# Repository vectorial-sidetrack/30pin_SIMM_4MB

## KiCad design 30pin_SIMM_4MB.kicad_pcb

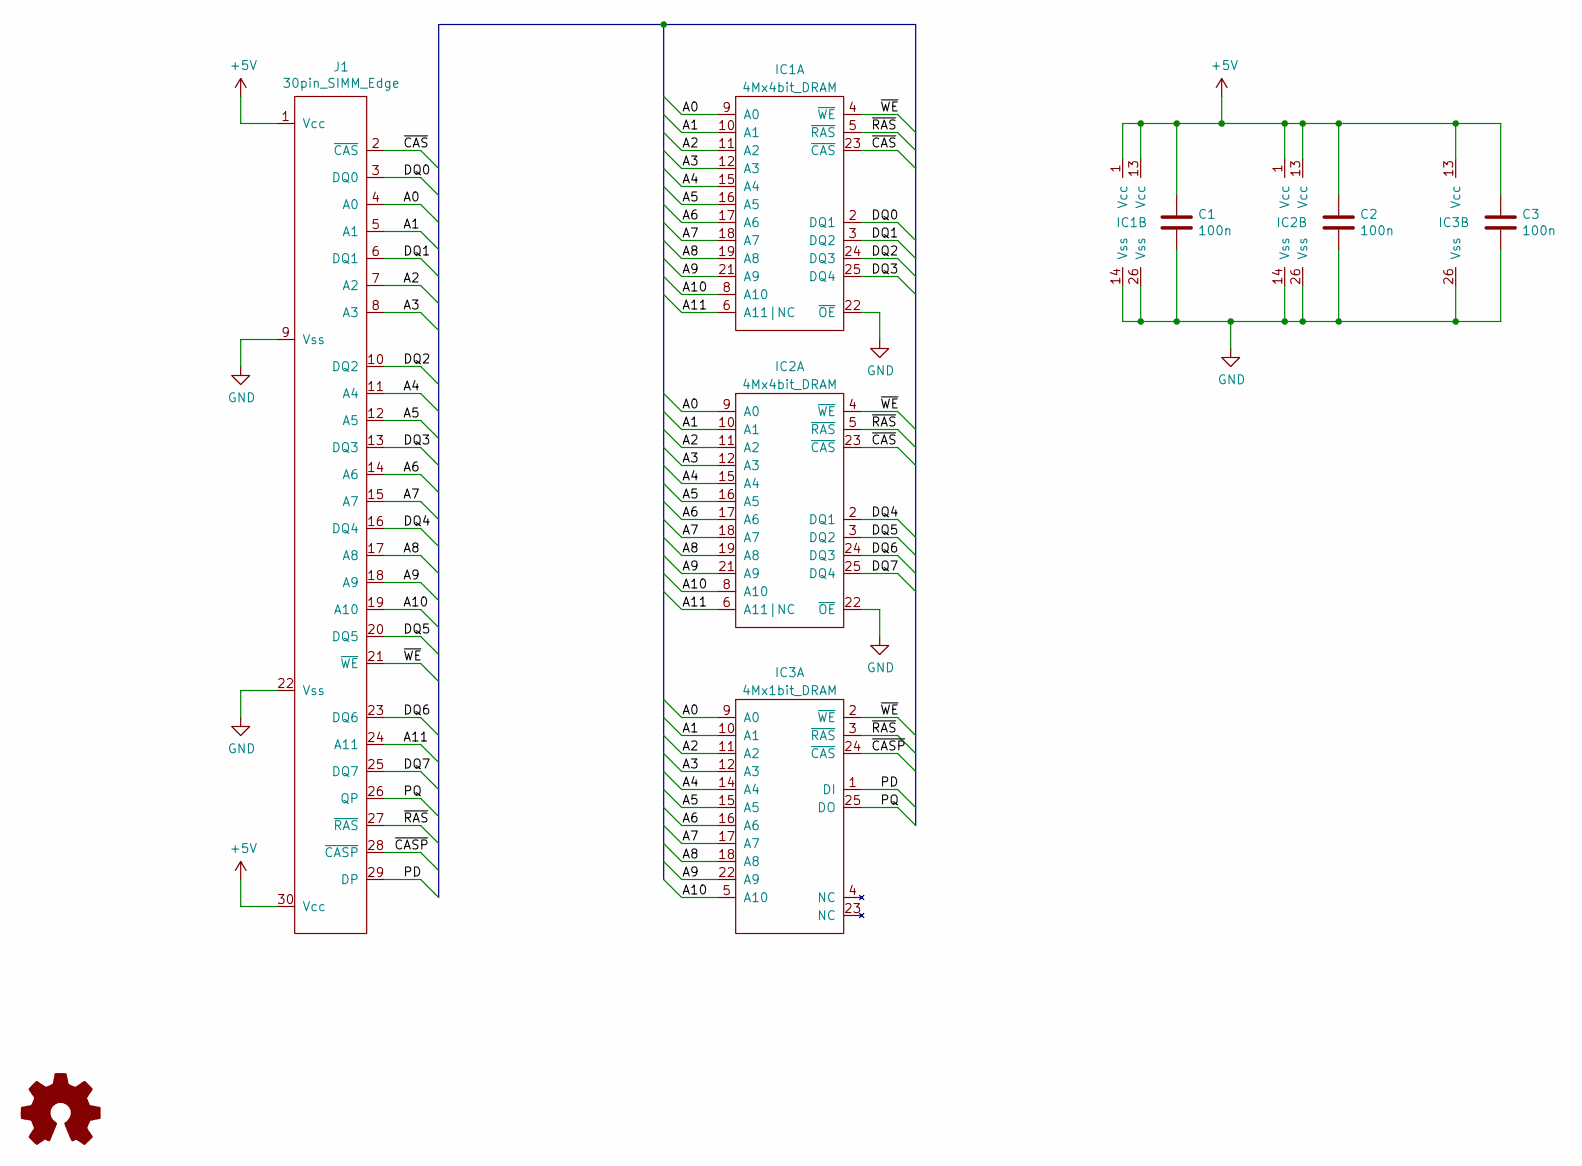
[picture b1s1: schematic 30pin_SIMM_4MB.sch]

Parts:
C1, C2, C3: 100n; C_1206_3216Metric
IC1, IC2: 4Mx4bit_DRAM; 4Mx4bit_DRAM_SOJ-24-26_7.5mm_HandSolder
IC3: 4Mx1bit_DRAM; 4Mx1bit_DRAM_SOJ-20-26_7.5mm_HandSolder
J1: 30pin_SIMM_Edge; 30pin_SIMM

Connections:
+5V: C1.1, C2.1, C3.1, IC1.1 (Vcc), IC1.13 (Vcc), IC2.1 (Vcc), IC2.13 (Vcc), IC3.13 (Vcc), J1.1 (Vcc), J1.30 (Vcc)
/A0: IC1.9 (A0), IC2.9 (A0), IC3.9 (A0), J1.4 (A0)
/A1: IC1.10 (A1), IC2.10 (A1), IC3.10 (A1), J1.5 (A1)
/A2: IC1.11 (A2), IC2.11 (A2), IC3.11 (A2), J1.7 (A2)
/A3: IC1.12 (A3), IC2.12 (A3), IC3.12 (A3), J1.8 (A3)
/A4: IC1.15 (A4), IC2.15 (A4), IC3.14 (A4), J1.11 (A4)
/A5: IC1.16 (A5), IC2.16 (A5), IC3.15 (A5), J1.12 (A5)
/A6: IC1.17 (A6), IC2.17 (A6), IC3.16 (A6), J1.14 (A6)
/A7: IC1.18 (A7), IC2.18 (A7), IC3.17 (A7), J1.15 (A7)
/A8: IC1.19 (A8), IC2.19 (A8), IC3.18 (A8), J1.17 (A8)
/A9: IC1.21 (A9), IC2.21 (A9), IC3.22 (A9), J1.18 (A9)
/A10: IC1.8 (A10), IC2.8 (A10), IC3.5 (A10), J1.19 (A10)
/A11: IC1.6 (A11|NC), IC2.6 (A11|NC), J1.24 (A11)
/DQ0: IC1.2 (DQ1), J1.3 (DQ0)
/DQ1: IC1.3 (DQ2), J1.6 (DQ1)
/DQ2: IC1.24 (DQ3), J1.10 (DQ2)
/DQ3: IC1.25 (DQ4), J1.13 (DQ3)
/DQ4: IC2.2 (DQ1), J1.16 (DQ4)
/DQ5: IC2.3 (DQ2), J1.20 (DQ5)
/DQ6: IC2.24 (DQ3), J1.23 (DQ6)
/DQ7: IC2.25 (DQ4), J1.25 (DQ7)
/PD: IC3.1 (DI), J1.29 (DP)
/PQ: IC3.25 (DO), J1.26 (QP)
/~CASP~: IC3.24 (~CAS~), J1.28 (~CASP~)
/~CAS~: IC1.23 (~CAS~), IC2.23 (~CAS~), J1.2 (~CAS~)
/~RAS~: IC1.5 (~RAS~), IC2.5 (~RAS~), IC3.3 (~RAS~), J1.27 (~RAS~)
/~WE~: IC1.4 (~WE~), IC2.4 (~WE~), IC3.2 (~WE~), J1.21 (~WE~)
GND: C1.2, C2.2, C3.2, IC1.14 (Vss), IC1.22 (~OE~), IC1.26 (Vss), IC2.14 (Vss), IC2.22 (~OE~), IC2.26 (Vss), IC3.26 (Vss), J1.9 (Vss), J1.22 (Vss)

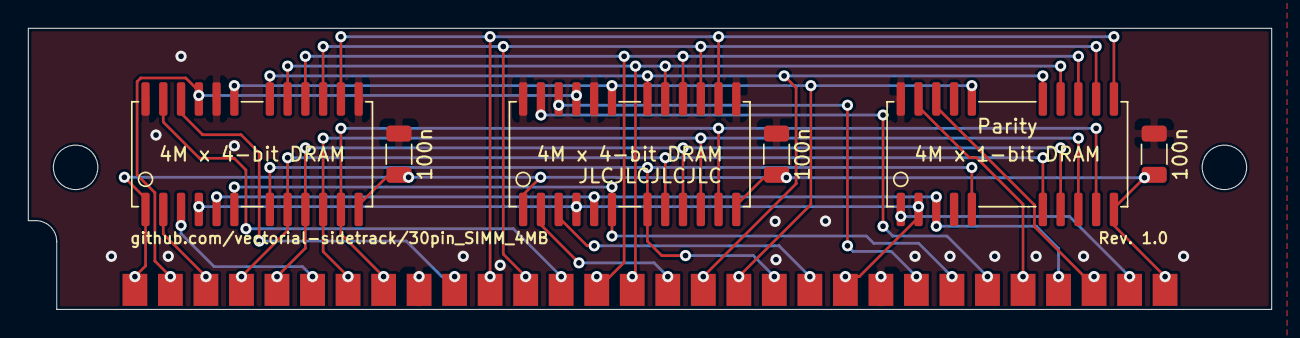
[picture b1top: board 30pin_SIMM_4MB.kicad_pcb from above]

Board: 2 copper layers, 88.9 x 20.1 mm, 7 parts (0 on the bottom side), 28 nets.

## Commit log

2021-02-21 Initial commit of local repository
2021-02-22 Added footprints with longer pads for hand soldering
2021-02-22 Created pcb template without traces
2021-02-22 Via placement for top pins
2021-02-22 Closer via spacing, larger traces
2021-02-22 Don't fear right angles
2021-02-22 Vias for bottom pads
2021-02-23 PCB Rev. 1.0 done
2021-02-23 Minor fixes
2021-02-23 GND Via placements and final edge cut outline
2021-02-23 Added silkscreen
2021-02-23 Added mounting holes as footprints and NPTH
2021-02-23 Added OSHW Logo to schematic
2021-02-23 Generate Gerber files
2021-02-23 Moved OSHW silkscreen to backside
2021-02-23 Updated gerber files
2021-02-23 Increased bottom edge clearance by 0.1 mm to 0.25 mm
